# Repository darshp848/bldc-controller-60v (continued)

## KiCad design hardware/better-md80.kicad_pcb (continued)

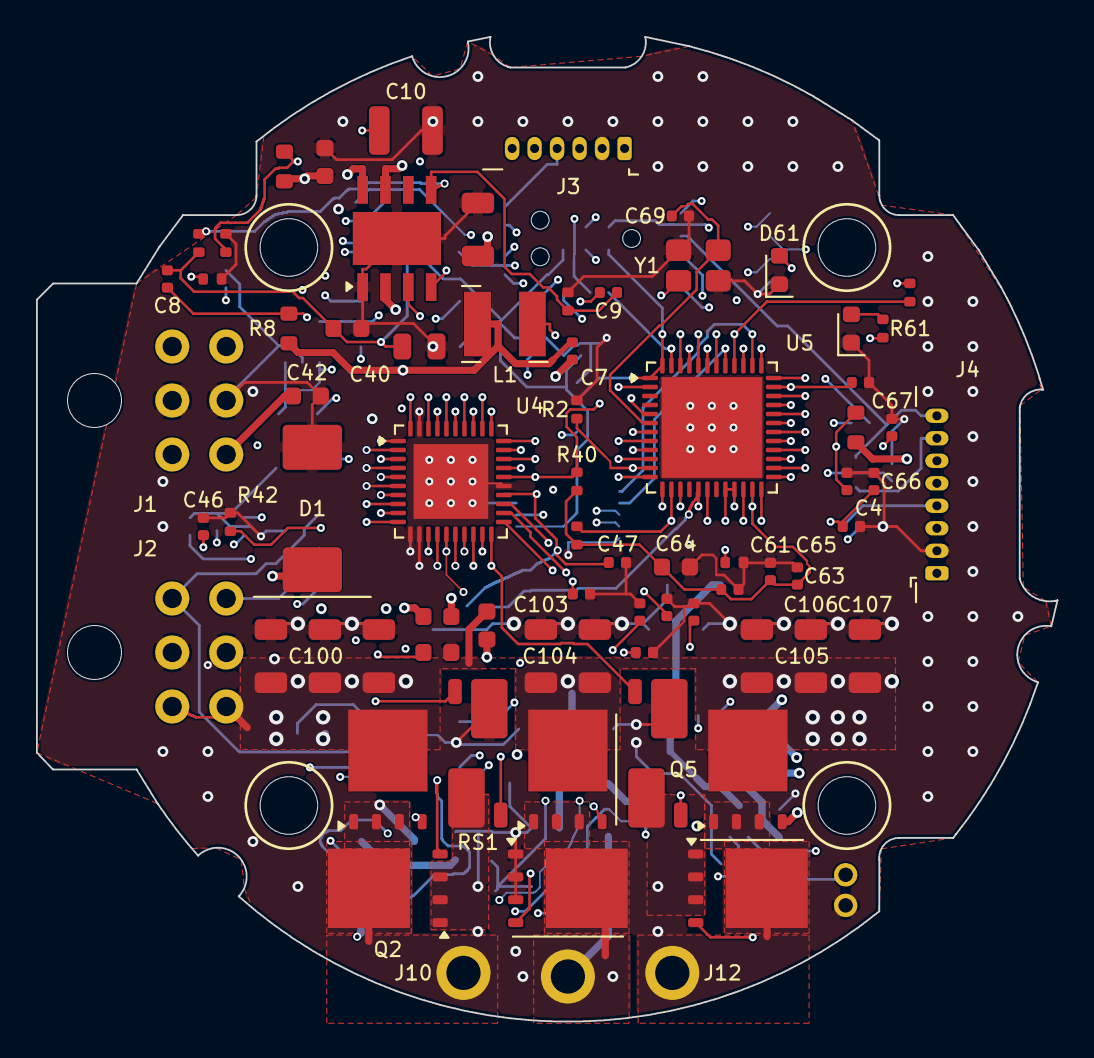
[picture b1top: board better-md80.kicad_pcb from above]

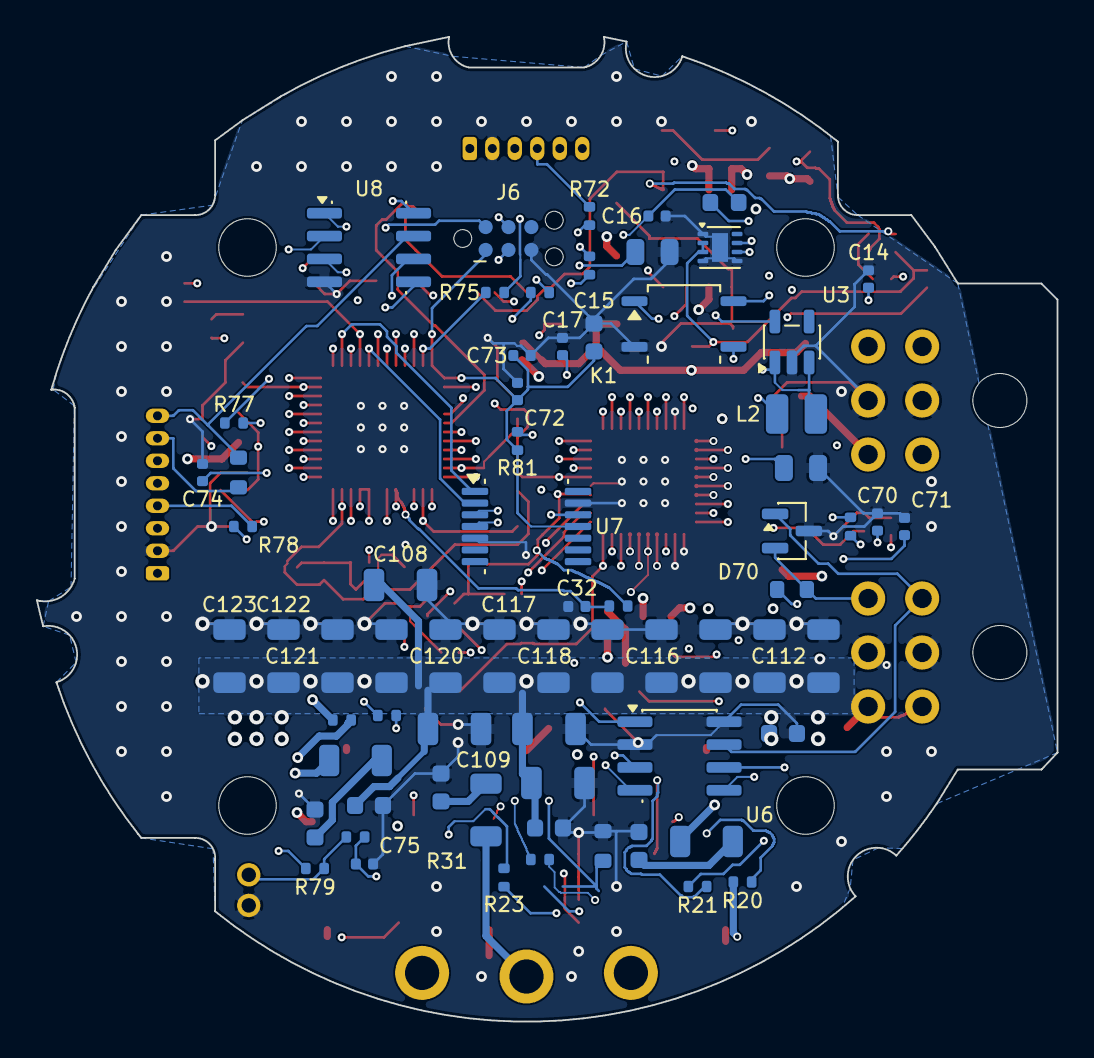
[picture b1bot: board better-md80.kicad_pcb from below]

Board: 6 copper layers, 56.7 x 54.7 mm, 144 parts (68 on the bottom side), 98 nets.

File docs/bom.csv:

"Refs","Value","Footprint","MPN","Qty","DNP","Note"
"C4","10n","Capacitor_SMD:C_0402_1005Metric","","1","",""
"C5,C100-C123","2.2u 100V","Capacitor_SMD:C_1206_3216Metric","TDK C3216X7S2A225K160AB","25","","DC-link row, 12 top + 12 bottom as on MD80"
"C6,C22,C26,C30,C42","100n 100V","Capacitor_SMD:C_0603_1608Metric","Murata GRM188R72A104KA35D","5","","Place across HS drain / LS source,VDRAIN local"
"C7","2.2n","Capacitor_SMD:C_0402_1005Metric","","1","",""
"C8","3.3n","Capacitor_SMD:C_0402_1005Metric","","1","",""
"C9","56p","Capacitor_SMD:C_0402_1005Metric","","1","",""
"C10","22u 25V","Capacitor_SMD:C_1210_3225Metric","Taiyo Yuden TMK325B7226KMHT","1","",""
"C11,C44,C45","1u 25V","Capacitor_SMD:C_0603_1608Metric","","3","",""
"C12,C40","10u 25V","Capacitor_SMD:C_0805_2012Metric","","2","",""
"C13","22u 10V","Capacitor_SMD:C_0805_2012Metric","","1","",""
"C14,C16,C46,C65,C73","1u","Capacitor_SMD:C_0402_1005Metric","","5","","VDDA"
"C15","2.2u","Capacitor_SMD:C_0603_1608Metric","","1","",""
"C17,C32,C47,C60-C63,C66,C67,C70-C72,C74,C75","100n","Capacitor_SMD:C_0402_1005Metric","","14","","VBAT,VREF,VREF+"
"C23,C27,C31","2.2n 100V","Capacitor_SMD:C_0603_1608Metric","","3","DNP",""
"C41","100n 25V","Capacitor_SMD:C_0402_1005Metric","","1","",""
"C43","47n 100V","Capacitor_SMD:C_0603_1608Metric","Murata GRM188R72A473KA01D (verify)","1","",""
"C48-C50","470p","Capacitor_SMD:C_0402_1005Metric","","3","","CSA output filter, at MCU pin"
"C64","4.7u","Capacitor_SMD:C_0603_1608Metric","","1","",""
"C68,C69","10p","Capacitor_SMD:C_0402_1005Metric","","2","",""
"D1","5.0SMDJ60A","Diode_SMD:D_SMC","Littelfuse 5.0SMDJ60A","1","","5 kW TVS, VRWM 60 V, VC 96.8 V @ 51.6 A; sized by sim/bus_surge.py"
"D60","Green","LED_SMD:LED_0603_1608Metric","Kingbright APTD1608LZGCK","1","",""
"D61","Red","LED_SMD:LED_0603_1608Metric","Kingbright APTD1608LSURCK","1","",""
"D70","PESD2CAN","Package_TO_SOT_SMD:SOT-23","Nexperia PESD2CAN,215","1","",""
"FB1","BLM18PG221","Inductor_SMD:L_0603_1608Metric","Murata BLM18PG221SN1D","1","",""
"J1,J2","Micro-Fit 2x3","better_md80:MD80_MicroFit_2x03_RA","Molex 43045-0600 (R/A, 2x3)","2","","Power + CAN daisy-chain, MD80 position; pinout see docs/mechanical.md"
"J3","AUX1 SPI enc","Connector_Molex:Molex_PicoBlade_53048-0610_1x06_P1.25mm_Horizontal","Molex 53048-0650","1","","MD80 AUX1 pinout"
"J4","AUX2 RS422","Connector_Molex:Molex_PicoBlade_53048-0810_1x08_P1.25mm_Horizontal","Molex 53048-0850","1","","MD80 AUX2 pinout"
"J5","Motor NTC","better_md80:MD80_NTC_Pads","","1","","Solder pads for MAB motor thermistor"
"J6","TC2030-NL","Connector:Tag-Connect_TC2030-IDC-NL_2x03_P1.27mm_Vertical","","1","",""
"J10","Phase A","better_md80:MD80_Phase_Pad","","1","","Motor lead solder pad"
"J11","Phase B","better_md80:MD80_Phase_Pad","","1","","Motor lead solder pad"
"J12","Phase C","better_md80:MD80_Phase_Pad","","1","","Motor lead solder pad"
"K1","CPC1017N","Package_SO:SOP-4_3.8x4.1mm_P2.54mm","IXYS CPC1017NTR","1","","Software termination switch (60 V PhotoMOS)"
"L1","47u","Inductor_SMD:L_Bourns-SRN4018","Bourns SRN4018-470M (verify Isat)","1","",""
"L2","2.2u","Inductor_SMD:L_1008_2520Metric","Murata DFE252012F-2R2M","1","",""
"MECH1","MD80 v3 holes","better_md80:MD80_V3_Mechanical","","1","","4x M2.5 holes + Micro-Fit peg holes at MD80 v3.0 coordinates"
"Q1-Q6","ISC022N10NM6","Package_TO_SOT_SMD:TDSON-8-1","Infineon ISC022N10NM6ATMA1","6","","100 V, 2.2 mOhm, SuperSO8"
"R1,R3","100k","Resistor_SMD:R_0603_1608Metric","","2","","UVLO on ~10.8 V,VBUS divider 20.6:1, 68 V -> 3.30 V"
"R2","5.1k","Resistor_SMD:R_0402_1005Metric","","1","",""
"R4","16.2k","Resistor_SMD:R_0402_1005Metric","","1","",""
"R5","75k","Resistor_SMD:R_0402_1005Metric","","1","","fsw = 12*2500/75k = 400 kHz"
"R6","453k","Resistor_SMD:R_0402_1005Metric","","1","","Vout = 1.2*(1+453/49.9) = 12.1 V"
"R7","49.9k","Resistor_SMD:R_0402_1005Metric","","1","",""
"R8","453k","Resistor_SMD:R_0603_1608Metric","","1","","Ripple injection (Type 3), per LM5164 EVM"
"R20-R25,R81","0","Resistor_SMD:R_0402_1005Metric","","7","","3.3 V mode: VDD3V3 tied to VDD,Gate resistor, tune for ringing"
"R30-R32","2.2","Resistor_SMD:R_1206_3216Metric","","3","DNP","RC snubber; fit on first boards (sim/double_pulse.py), 0.3 W"
"R33,R40,R41,R60,R79","10k","Resistor_SMD:R_0402_1005Metric","","5","",""
"R42","100k","Resistor_SMD:R_0402_1005Metric","","1","",""
"R61,R62,R80","1k","Resistor_SMD:R_0402_1005Metric","","3","",""
"R70","680","Resistor_SMD:R_0402_1005Metric","","1","",""
"R71,R76","120","Resistor_SMD:R_0603_1608Metric","","2","","RX termination"
"R72-R75","33","Resistor_SMD:R_0402_1005Metric","","4","",""
"R77,R78","100","Resistor_SMD:R_0402_1005Metric","","2","",""
"RS1,RS3","0.5m","Resistor_SMD:R_Shunt_Vishay_WSK2512_6332Metric_T2.66mm","Vishay WSK2512 0.5 mOhm 1% (verify)","2","","Kelvin 4-terminal, top side between the FETs"
"TH1","10k NTC","Resistor_SMD:R_0603_1608Metric","Murata NCP18XH103F03RB","1","","Place between phase B FETs"
"U1","LM5164DDAR","Package_SO:Texas_HSOP-8-1EP_3.9x4.9mm_P1.27mm","TI LM5164DDAR","1","","100 V, 1 A COT sync buck; 12 V rail for gate drive"
"U2","TPS62163DSGR","Package_SON:Texas_DSG0008A_WSON-8-1EP_2x2mm_P0.5mm_EP0.9x1.6mm","TI TPS62163DSGR","1","","Fixed 5.0 V, 1 A; FB tied to GND for fixed version"
"U3","TLV75533PDBVR","Package_TO_SOT_SMD:SOT-23-5","TI TLV75533PDBVR","1","",""
"U4","DRV8353SRTAR","Package_DFN_QFN:Texas_RHA0040B_VQFN-40-1EP_6x6mm_P0.5mm_EP4.15x4.15mm","TI DRV8353SRTAR","1","","VM from 12 V rail so gate-drive losses do not scale with VBUS"
"U5","STM32G474CEU6","Package_DFN_QFN:QFN-48-1EP_7x7mm_P0.5mm_EP5.6x5.6mm","ST STM32G474CEU6","1","","170 MHz M4F, HRTIM, FDCAN, 5x ADC"
"U6","TCAN1044AVDR","Package_SO:SOIC-8_3.9x4.9mm_P1.27mm","TI TCAN1044AVDR","1","","8 Mbit/s CAN-FD, VIO 3.3 V; TJA1051T/3 pinout"
"U7","AS5047P-ATSM","Package_SO:TSSOP-14_4.4x5mm_P0.65mm","ams OSRAM AS5047P-ATSM","1","","14-bit on-axis encoder, bottom side at rotation axis, same TSSOP-14 height as MD80"
"U8","MAX3490EESA+","Package_SO:SOIC-8_3.9x4.9mm_P1.27mm","Analog MAX3490EESA+","1","","Full-duplex RS-422 for AksIM-2 / Orbis"
"Y1","8MHz","Crystal:Crystal_SMD_3225-4Pin_3.2x2.5mm","Abracon ABM8-8.000MHZ-B2-T (verify CL)","1","","HSE for FDCAN bit timing at 8 Mbit/s"

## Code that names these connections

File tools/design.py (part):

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
# Micro-Fit 2x3 R/A. Pads 1-3: row nearest board edge (housing bottom row),
# 4-6: rear row. Column order CAN / GND / VBUS, per MAB's connector diagram.
MICROFIT_PINS = {"1": "CANH", "2": "GND", "3": "VBUS", "4": "CANL", "5": "GND", "6": "VBUS"}

SHEETS = []

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    R("R40", "10k", "+3V3", "DRV_nFAULT"),
    R("R41", "10k", "+3V3", "DRV_MISO"),
    R("R42", "100k", "DRV_EN", "GND"),
    C("C48", "470p", "SOA", "GND", note="CSA output filter, at MCU pin"),
    C("C49", "470p", "SOB", "GND"),
    C("C50", "470p", "SOC", "GND"),
])
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    "33": "CAN_RX", "34": "CAN_TX", "36": "SWDIO", "37": "SWCLK", "38": "ENC_nCS",
    "17": "TEMP_FET", "18": "TEMP_MOTOR",
    "41": "SPI3_SCK", "42": "SPI3_MISO", "43": "SPI3_MOSI",
    "44": "AUX_GPIO1", "45": "AUX_GPIO2", "46": "BOOT0", "47": "AUX_nCS",
    "22": "RS422_TX", "24": "RS422_RX", "25": "CAN_TERM_EN",
    "29": "DRV_EN", "39": "DRV_nFAULT", "40": "LED_RED", "2": "LED_GREEN",
    "5": "HSE_IN", "6": "HSE_OUT", "7": "NRST",
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    C("C74", "100n", "+3V3", "GND"),
    R("R76", "120", "RS422_A", "RS422_B", "0603", note="RX termination"),
    Part("J4", "Connector_Generic:Conn_01x08", "AUX2 RS422",
         {"1": "+5V", "2": "GND", "3": "AUX_GPIO1_C", "4": "AUX_GPIO2_C", "5": "RS422_Y", "6": "RS422_Z",
          "7": "RS422_A", "8": "RS422_B"}, FP["AUX2"], "Molex 53048-0850", note="MD80 AUX2 pinout"),
    R("R77", "100", "AUX_GPIO1", "AUX_GPIO1_C"),
    R("R78", "100", "AUX_GPIO2", "AUX_GPIO2_C"),
    Part("J5", "Connector_Generic:Conn_01x02", "Motor NTC", {"1": "TEMP_MOTOR_C", "2": "GND"}, FP["NTC"],
         "", note="Solder pads for MAB motor thermistor"),
    R("R79", "10k", "+3V3A", "TEMP_MOTOR_C"),
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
